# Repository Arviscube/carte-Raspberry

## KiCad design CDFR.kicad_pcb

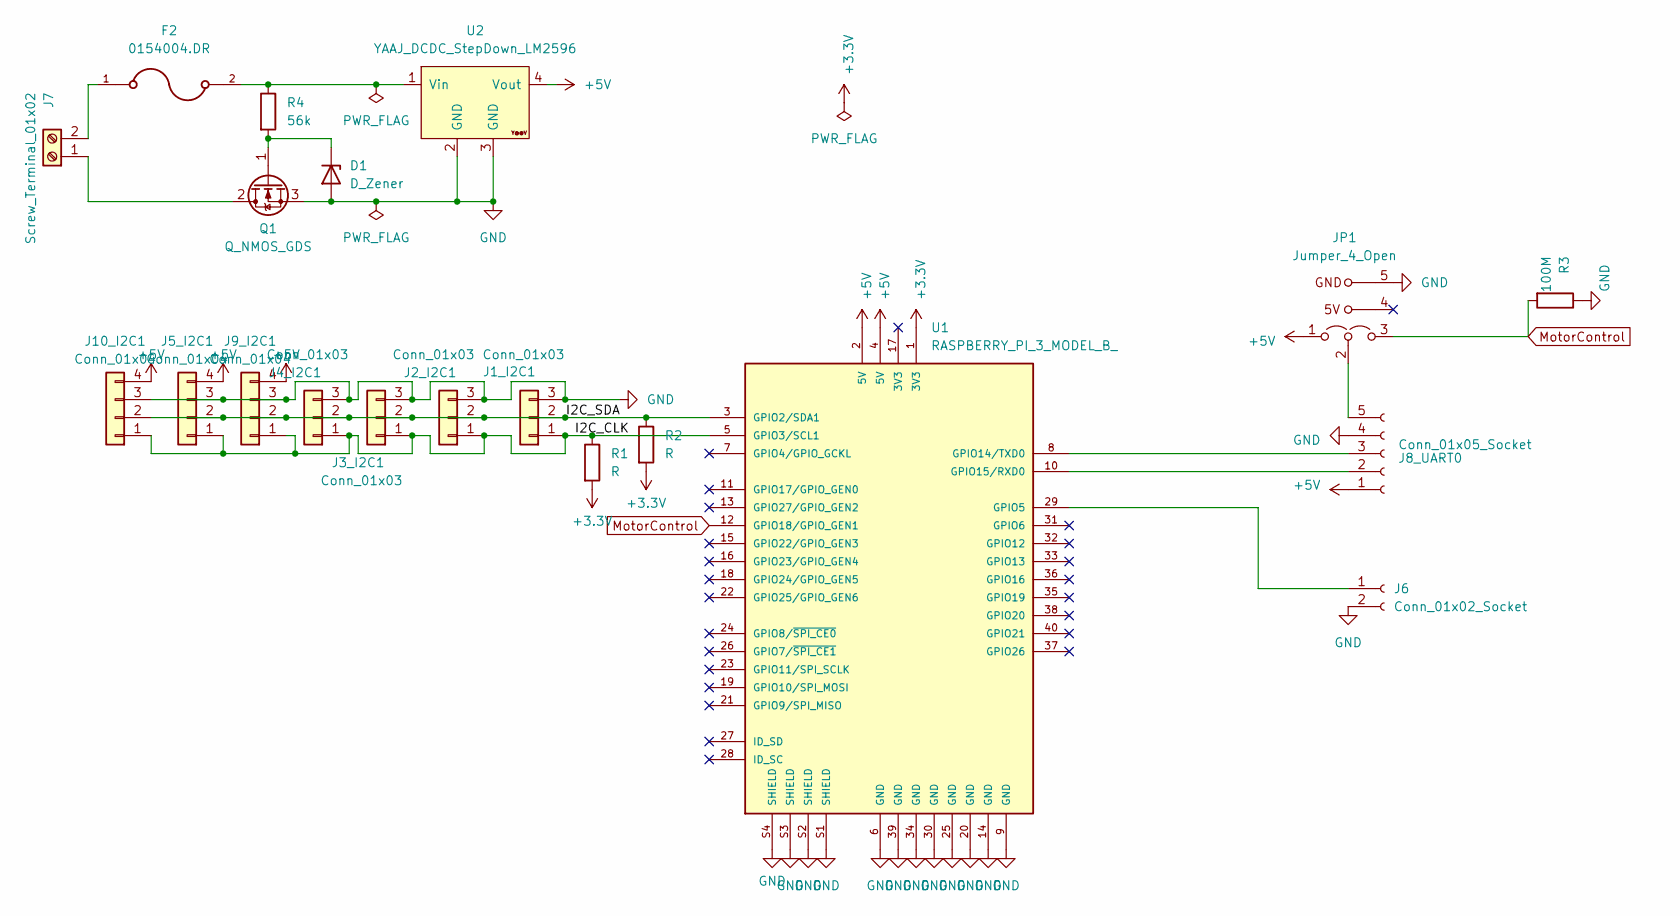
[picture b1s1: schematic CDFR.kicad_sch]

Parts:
D1: D_Zener; D_SOD-123
F2: 0154004.DR; FUSE_0154004.DR
J1_I2C1, J2_I2C1, J3_I2C1, J4_I2C1: Conn_01x03; JST_XH_B3B-XH-A_1x03_P2.50mm_Vertical
J5_I2C1, J9_I2C1, J10_I2C1: Conn_01x04; JST_XH_B4B-XH-A_1x04_P2.50mm_Vertical
J6: Conn_01x02_Socket; PinHeader_1x02_P2.54mm_Vertical
J7: Screw_Terminal_01x02; CUI_TBP01R1-508-02BE
J8_UART0: Conn_01x05_Socket; JST_XH_B5B-XH-A_1x05_P2.50mm_Vertical
JP1: Jumper_4_Open; jumper_4_pole
Q1: Q_NMOS_GDS; TO-252-2
R1, R2: R; R_0603_1608Metric_Pad0.98x0.95mm_HandSolder
R3: 100M; R_0603_1608Metric_Pad0.98x0.95mm_HandSolder
R4: 56k; R_0603_1608Metric_Pad0.98x0.95mm_HandSolder
U1: RASPBERRY_PI_3_MODEL_B_; EmpreintPourShiel_RaspberryPi3B; PARTREV N/A
U2: YAAJ_DCDC_StepDown_LM2596

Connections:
+3.3V: R1.2, R2.2, U1.1 (3V3)
+5V: J5_I2C1.4, J8_UART0.1, J9_I2C1.4, J10_I2C1.4, JP1.1 (A), U1.2 (5V), U1.4 (5V), U2.4 (Vout)
/I2C_CLK: J1_I2C1.1, J2_I2C1.1, J3_I2C1.1, J4_I2C1.1, J5_I2C1.1, J9_I2C1.1, J10_I2C1.1, R1.1, U1.5 (GPIO3/SCL1)
/I2C_SDA: J1_I2C1.2, J2_I2C1.2, J3_I2C1.2, J4_I2C1.2, J5_I2C1.2, J9_I2C1.2, J10_I2C1.2, R2.1, U1.3 (GPIO2/SDA1)
GND: D1.2 (A), J1_I2C1.3, J2_I2C1.3, J3_I2C1.3, J4_I2C1.3, J5_I2C1.3, J6.2, J8_UART0.4, J9_I2C1.3, J10_I2C1.3, JP1.5 (A), Q1.3 (S), R3.1, U1.6 (GND), U1.9 (GND), U1.14 (GND), U1.20 (GND), U1.25 (GND), U1.30 (GND), U1.34 (GND), U1.39 (GND), U1.S1 (SHIELD), U1.S2 (SHIELD), U1.S3 (SHIELD), U1.S4 (SHIELD), U2.2 (GND), U2.3 (GND)
MotorControl: JP1.3 (B), R3.2, U1.12 (GPIO18/GPIO_GEN1)
unnamed: D1.1 (K), Q1.1 (G), R4.2
unnamed: J6.1, U1.29 (GPIO5)
unnamed: J7.1, Q1.2 (D)
unnamed: F2.1, J7.2
unnamed: J8_UART0.2, U1.10 (GPIO15/RXD0)
unnamed: J8_UART0.3, U1.8 (GPIO14/TXD0)
unnamed: J8_UART0.5, JP1.2 (C)
unnamed: F2.2, R4.1, U2.1 (Vin)

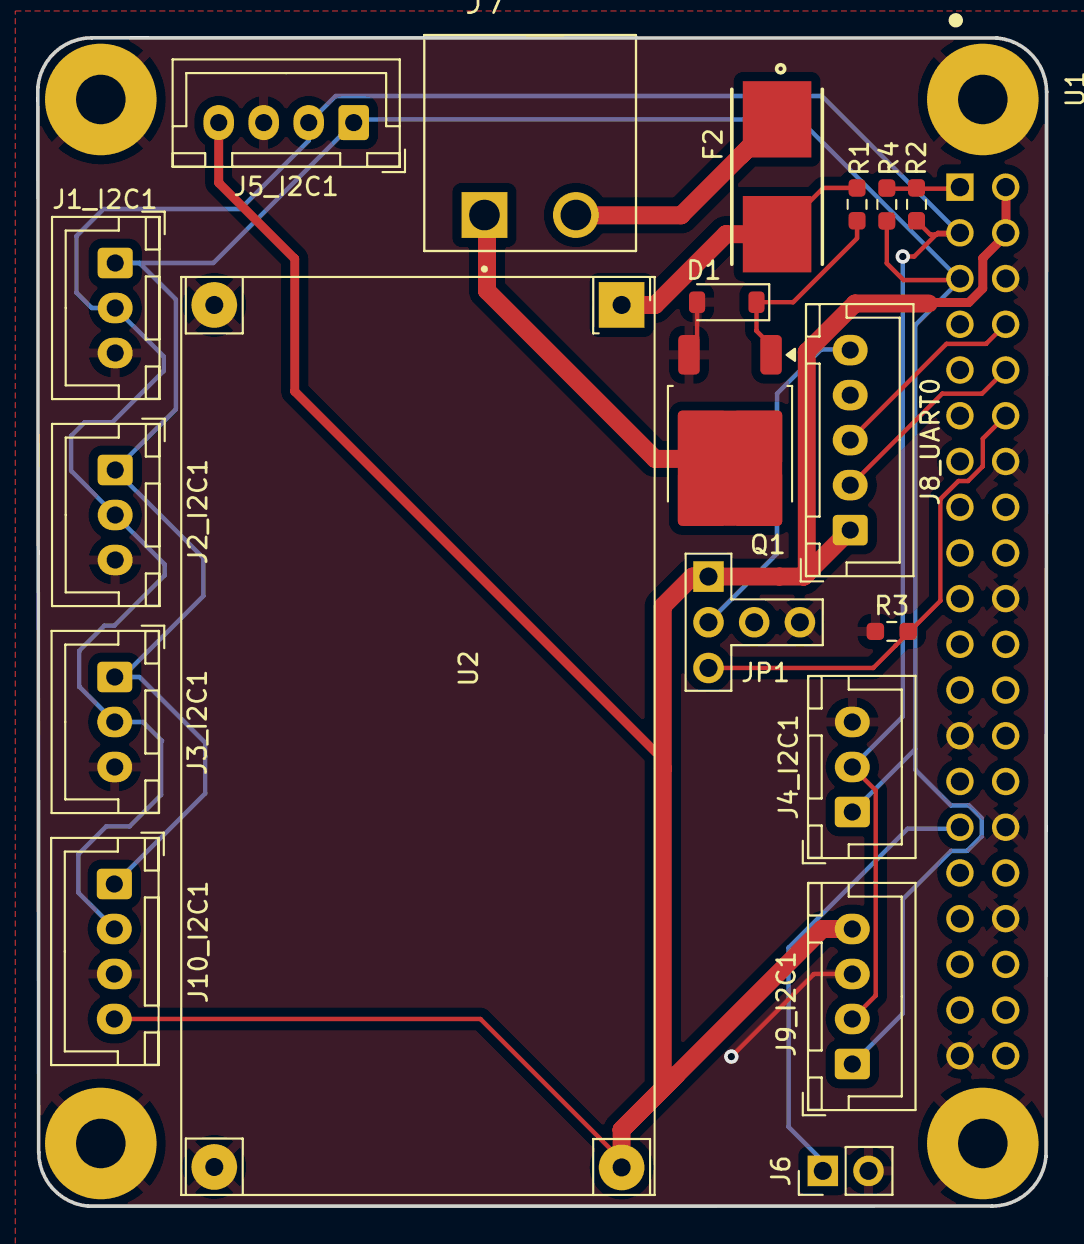
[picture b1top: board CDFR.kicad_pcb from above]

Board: 2 copper layers, 56.0 x 64.9 mm, 20 parts (0 on the bottom side), 14 nets.

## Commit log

2025-08-03 update gitignores
2025-08-03 commande
